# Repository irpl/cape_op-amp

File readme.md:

# Inverting Op-Amp Amplifier – Schematic & PCB

## Overview

This repository contains the schematic and PCB design for an inverting operational amplifier (op-amp) experiment board.
The board is intended for educational and laboratory use, allowing users to explore closed-loop gain, feedback, and signal behaviour in a practical, hands-on way.

The circuit implements a classic inverting amplifier configuration, where the gain is determined by the ratio of the feedback and input resistors selected during board population.

## Circuit Description

The op-amp is configured as an inverting amplifier with:

- Configurable input resistor (Rin)
- Configurable feedback resistor (Rf)
- Closed-loop gain defined by:

$$
𝐴_{0} = −\frac{𝑅_𝑓}{𝑅_{𝑖}}
$$

By choosing different resistor values, users can easily experiment with different gain magnitudes while observing the effect on the output signal.

## Power Supply

The PCB includes dedicated power supply terminals to support flexible operation:

- Designed to work with dual-rail supplies (e.g. ±9 V, ±12 V, ±15 V)
- Supply rails are clearly labeled on the PCB
- No onboard regulation is included — the op-amp is powered directly from the external supply

> ⚠️ Ensure the selected op-amp is operated within its specified supply voltage limits.

## Test & Measurement Points

To support analysis and troubleshooting, the board includes clearly marked probe pads for oscilloscope or multimeter connections:

- Input signal (Vin)
- Output signal (Vout)
- Ground reference
- (Optional) supply rail probe points, if populated

These pads allow users to:

- Measure gain directly
- Observe phase inversion
- Inspect clipping and saturation
- Compare theoretical vs measured performance

## Intended Use

This board is suitable for:

- Op-amp laboratory experiments
- Demonstrating inverting amplifier behaviour
- Teaching closed-loop gain and feedback concepts
- Signal measurement with oscilloscopes and function generators
- Quick resistor-swap experiments without rewiring a breadboard

## Repository Contents

- Schematic files – complete circuit diagram of the inverting amplifier
- PCB layout files – board layout matching the schematic
- (Optional) Gerber files – for PCB fabrication
- This README

## Notes & Best Practices

- Populate only one set of input/feedback resistors at a time unless explicitly designed for parallel options.
- Use precision resistors for accurate gain measurements.
- Always connect the ground reference of the signal generator and oscilloscope to the PCB ground.
- Avoid driving the output beyond the op-amp’s output swing limits to prevent distortion.

## License / Usage

This design is intended for educational and experimental use.
Feel free to modify and adapt it for teaching, labs, or personal projects.

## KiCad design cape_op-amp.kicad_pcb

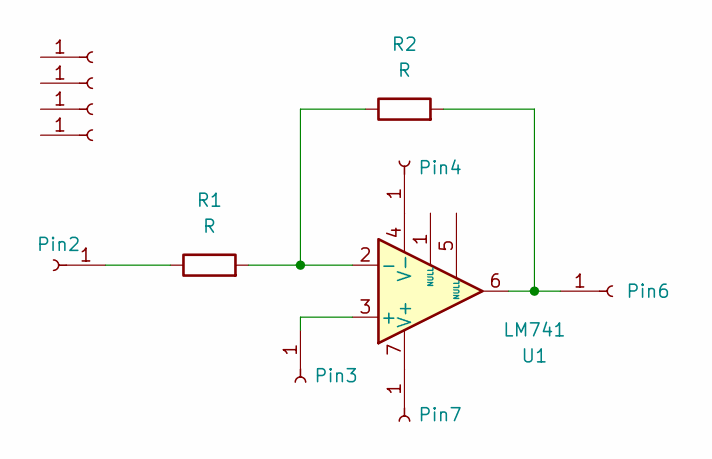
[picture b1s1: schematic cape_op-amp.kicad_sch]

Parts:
J1, J2, J3, J4: Conn_01x01_Socket; MountingHole_4.3mm_M4_Pad_Via
Pin2, Pin3, Pin6, Pin7: Conn_01x01_Socket; MountingHole_4.3mm_M4_Pad
Pin4: Conn_01x01_Socket; MountingHole_3.5mm_Pad
R1, R2: R; R_Axial_DIN0207_L6.3mm_D2.5mm_P15.24mm_Horizontal
U1: LM741; DIP-8_W7.62mm_LongPads-cape

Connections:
unnamed: Pin2.1, R1.1
unnamed: Pin3.1, U1.3 (+)
unnamed: Pin4.1, U1.4 (V-)
unnamed: Pin6.1, R2.2, U1.6
unnamed: Pin7.1, U1.7 (V+)
unnamed: R1.2, R2.1, U1.2 (-)

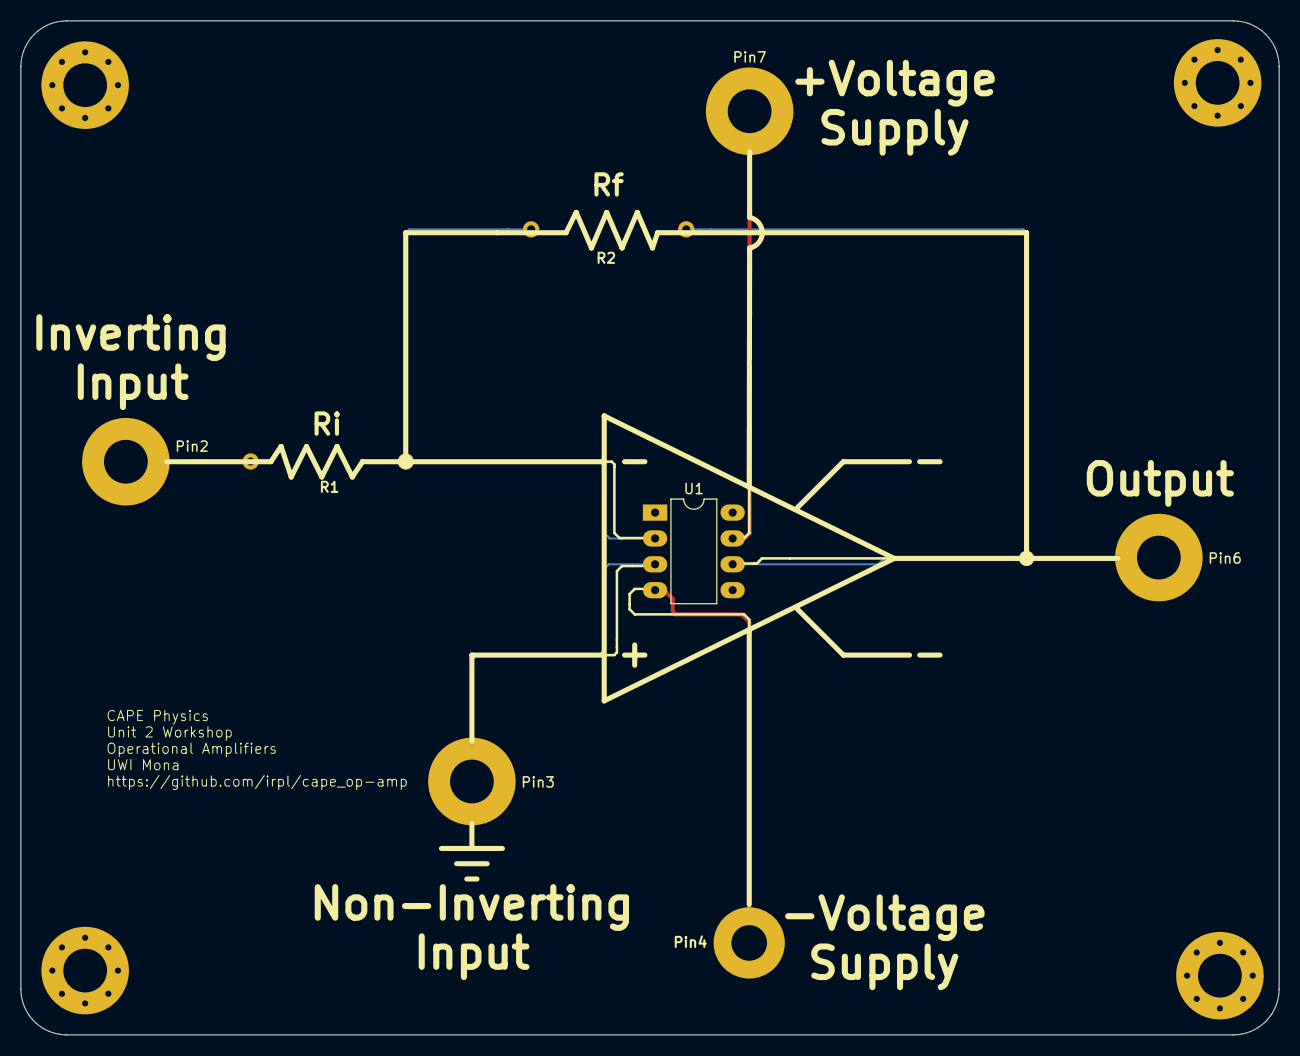
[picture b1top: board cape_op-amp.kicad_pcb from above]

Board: 2 copper layers, 123.6 x 99.6 mm, 12 parts (0 on the bottom side), 6 nets.

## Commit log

2026-01-15 made power traces thicker
2026-01-15 added a readme
2026-01-15 added images
2026-01-15 images in readme
2026-01-15 formatting
2026-01-15 added github link to readme
